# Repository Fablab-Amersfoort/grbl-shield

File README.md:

Grbl shield
-----------

This repository contains the KiCad design files for a grbl shield. It is
intended to for an Arduino Uno running [grbl][1], to connect it to
external stepper drivers, limit switches and other equipment. The reason
for developing this shield, instead of using an existing shield, is that
this shield has filtering applied to the limit pins to allow more robust
operation in a noisy environment (at [Fablab Amersfoort][2], our limit
switches were picking up noise from the parallely running spindle power
wires). Other than that, this is a trivial PCB, that just connects pin
headers to the Arduino pins.

[1]: https://github.com/grbl/grbl/
[2]: http://www.fablabamersfoort.nl

The repository contains the KiCad design files for the board, under
"Releases" in github we also have pre-generated gerber files to use. We
have a few spare boards from our own order, which you can [order through
tindie][tindie].

[tindie]: https://www.tindie.com/products/12515/

Grbl pinout
-----------
This shield supports both the old (0.8) and new (0.9) Grbl pinout. The
difference is that the limit Z and spindle enable pins are swapped, and
the latter is repurposed to a spindle PWM pin. For the spindle,
switching layouts is a matter of use the right connector (`SPIN_EN` or
`SPIN_PWM`), but for the z limit pin, a solder jumper needs to be
soldered in either position (since there is also a filter attached).

Ground connections
------------------
The shield connects all three Arduino ground pins to the ground plane.
Ideally, you would use only one pin to prevent ground loops, but I
wasn't sure which one to use. The one above the digital pins is very
close to the limit pin connector and filter, but looking at the Arduino
Uno schematic, there is quite some distance and some vias between that
pins and the microcontroller. The other two ground pins have a better
connection to the microcontroller, but are further away from the limit
pins. For now, all of them are connected, if this causes problems, we
could try disconnecting some ground pins.

SMD capacitors
--------------
The shield uses SMD components for the filter capacitors, to minimize
the distance (and inductance) from the filtered pins and the capacitors.
To simplify the layout, the resistors use through-hole versions instead.

In the prototype, 22nF was used, but in the final design these were
replaced by 10nF because that was what was available.

Empty components
----------------
A number of components on the limit pins are left empty (NC) in the
schematic. Initial testing shows these shouldn't be needed, but if
further problems crop up, they could be used to improve the stability of
the design by adding smaller pullup resistors (Arduino Uno internal ones
are fairly big at 20k-50k), or adding a second filter capacitor of a
different size.

Single-sided layout
-------------------
The original layout was made for single-sided milling on a CNC mill, so
the design does not use any vias. The v1 board was produced like
this, v2 was slightly modified for 2-layer commercial production (but it
should be easy to make it single-sided again).

License
-------
This design is made available under the CERN Open Hardware License,
version 1.2 or above. See LICENSE.txt for the full text of the license.

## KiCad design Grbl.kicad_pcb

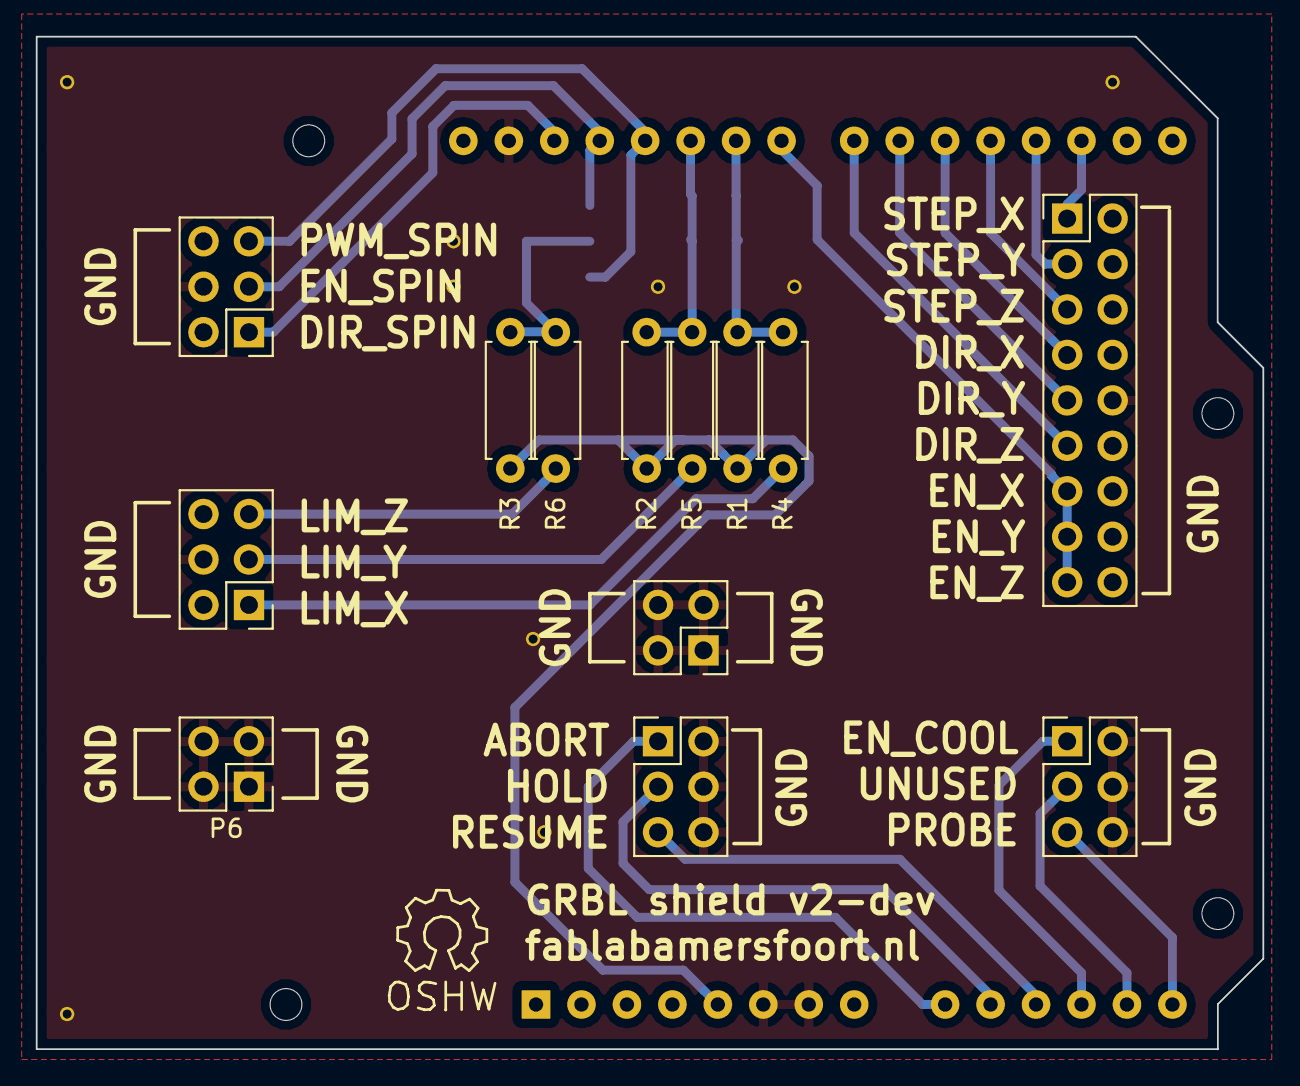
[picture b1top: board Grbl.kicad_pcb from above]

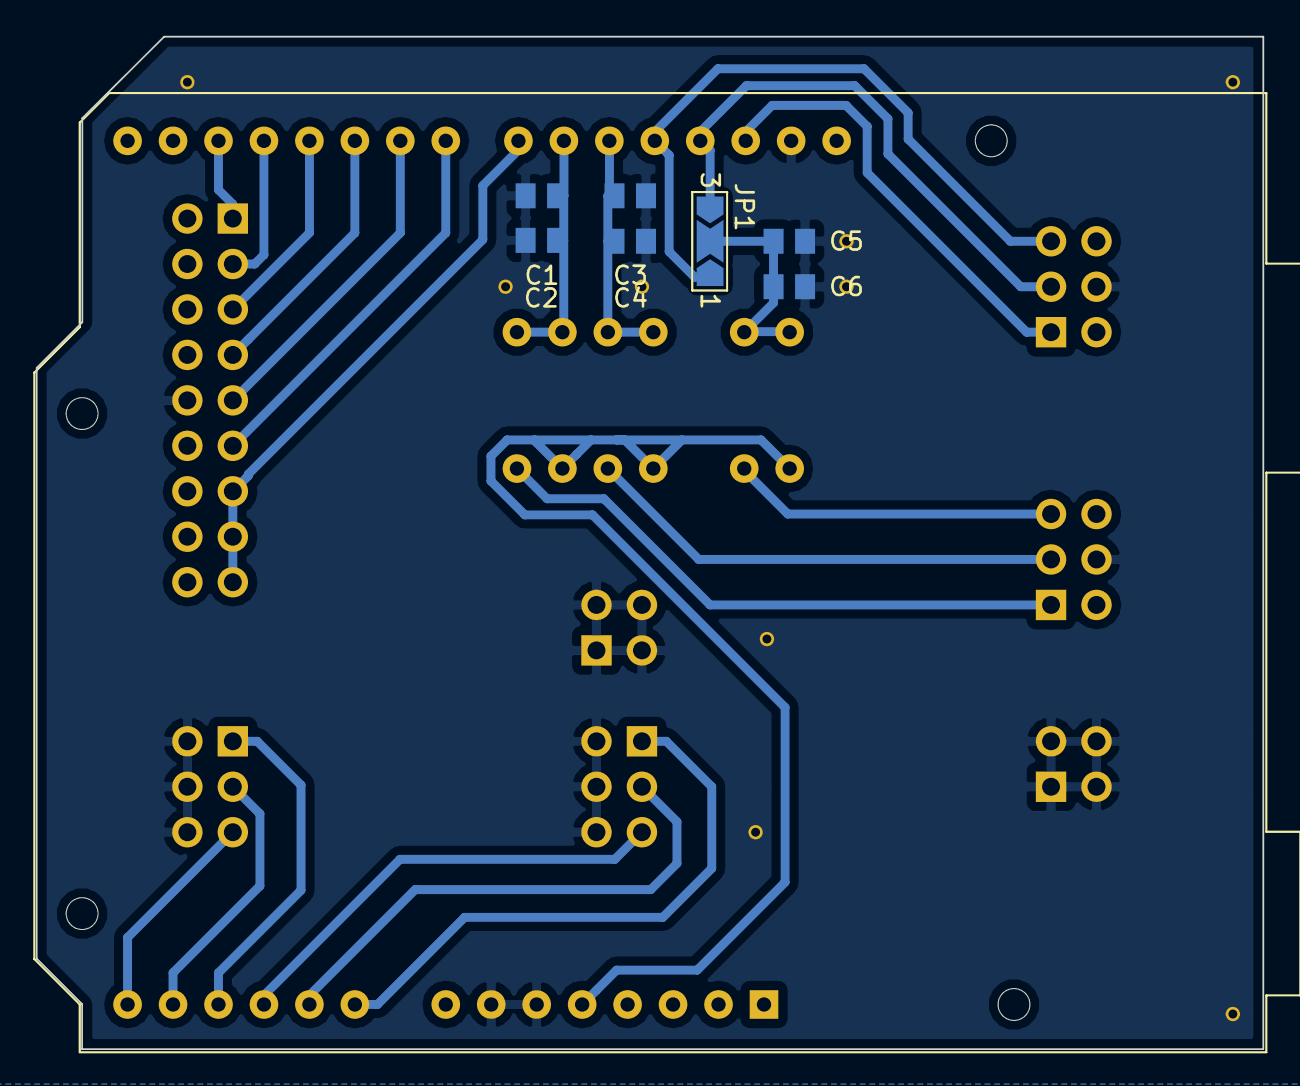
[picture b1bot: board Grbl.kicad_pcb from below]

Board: 2 copper layers, 68.5 x 56.6 mm, 21 parts (8 on the bottom side), 24 nets.

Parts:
C1, C3, C5: 10n; C_0805_2012Metric
C2, C4, C6: NC; C_0805_2012Metric
JP1: LAYOUT; SolderJumper-3_P2.0mm_Open_TrianglePad1.0x1.5mm_NumberLabels
P1: CTL; PinHeader_2x03_P2.54mm_Vertical
P2: MISC; PinHeader_2x03_P2.54mm_Vertical
P3: STEP; PinHeader_2x09_P2.54mm_Vertical
P4: SPIN; PinHeader_2x03_P2.54mm_Vertical
P5: LIMIT; PinHeader_2x03_P2.54mm_Vertical
P6, P7: GND; PinHeader_2x02_P2.54mm_Vertical
R1, R2, R3: NC; R_Axial_DIN0207_L6.3mm_D2.5mm_P7.62mm_Horizontal
R4, R5, R6: 1K; R_Axial_DIN0207_L6.3mm_D2.5mm_P7.62mm_Horizontal
SHIELD1: ARDUINO_UNO; Arduino_UNO_R2_WithMountingHoles

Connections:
+5V: R1.2, R2.2, R3.2, SHIELD1.5
/ABORT: P1.1, SHIELD1.9
/DIR_SPIN: P4.1, SHIELD1.28
/DIR_X: P3.7, SHIELD1.20
/DIR_Y: P3.9, SHIELD1.21
/DIR_Z: P3.11, SHIELD1.22
/EN_COOL: P2.1, SHIELD1.12
/EN_SPIN: JP1.3, P4.3, SHIELD1.27
/EN_X: P3.13, P3.15, P3.17, SHIELD1.23
/HOLD: P1.3, SHIELD1.10
/LIM_X: P5.1, R4.2
/LIM_X_FILTERED: C1.1, C2.1, R1.1, R4.1, SHIELD1.24
/LIM_Y: P5.3, R5.2
/LIM_Y_FILTERED: C3.1, C4.1, R2.1, R5.1, SHIELD1.25
/LIM_Z: P5.5, R6.2
/LIM_Z_FILTERED: C5.1, C6.1, JP1.2, R3.1, R6.1
/PROBE: P2.5, SHIELD1.14
/PWM_SPIN: JP1.1, P4.5, SHIELD1.26
/RESUME: P1.5, SHIELD1.11
/STEP_X: P3.1, SHIELD1.17
/STEP_Y: P3.3, SHIELD1.18
/STEP_Z: P3.5, SHIELD1.19
/UNUSED: P2.3, SHIELD1.13
GND: C1.2, C2.2, C3.2, C4.2, C5.2, C6.2, P1.2, P1.4, P1.6, P2.2, P2.4, P2.6, P3.10, P4.4, P5.4, P6.1, P6.2, P6.3, P6.4, P7.1, P7.2, P7.3, P7.4, SHIELD1.6, SHIELD1.7, SHIELD1.29

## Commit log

2015-12-20 Empty initial commit
2015-12-21 Add first version of the KiCad design files
2017-07-06 Add .gitignore file
2017-07-06 Close the outline
    There was a tiny hole in the top right corner.
2017-07-06 Remove no longer existing library
    The Arduino symbol itself is still in the cache, but future designs
    should probably use the symbol shipped with KiCad instead.
2017-07-06 Add more ground pins
    This helps connecting the shield wire of cables.
2017-07-06 Update silkscreen for two-layer version
    For the milled single layer version, there was copper on the back and
    "silkscreen" on the front. For a 2-layer version, there can be
    silkscreen on the back.
    This moves the refdes for capacitors to the back and removes the JP1
    label.
2017-07-06 Add a groundplane on the front
    This adds a filled zone and some vias.
2017-07-06 Add "GRBL shield v2" to the silkscreen
2017-07-06 Connect mounting holes to GND
    This changes the netname of the pads in the footprint, which won't
    survive a netleast re-read. There might be better approaches, but for
    now this works.
2017-07-06 Move some traces out of the way
    These were conflicting with the recently added GND header.
2017-07-06 Note single vs double-sided in the README
2017-07-07 Add board dimension markers
    These are just informative and will not show up on the board.
2017-07-07 Update plot options for Seeed
2017-07-09 Add a license notice
2017-07-18 Correct silkscreen for spindle pins
    These accidentially had the PWM_SPIN and DIR_SPIN labels swapped.
2018-05-17 README: Fix weird wording
2018-05-17 README: Add image of assembled board
2018-05-17 Convert design to KiCad 5, with some changes
    This converts the design to use the newer KiCad 5 symbols and
    footprints, but additionally makes some changes:
    - The Arduino Uno symbol is now one from the default library instead of a
    third-party symbol, but it has a different pin numbering and layout.
    - The limit pin filtering schematic is a bit more spaced out, using net
    labels instead of direct connections.
2018-05-17 README: Remove improvements
    The solder jumper was already made bigger, and making the traces bigger
    is only relevant when milling this manually, which I'll probably not be
    doing.
2018-05-18 README: Add tindie link
